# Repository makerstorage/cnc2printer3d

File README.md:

This Project is for the people who have their own desktop CNC machine and wish to use it as a 3D printer. Over the years We have had lots of good feedback about the subject and so decided to develop Hardware and Software solutions for makers. 

For more details, check out the project pages at

https://cnc2printer3d.wordpress.com/

And our store at

http://makerstorage.com/index.php

We enjoy sharing theses ideas with you all and any contributions, comments and or feedback is invited.

Community, Collaboration and Sharing is our most important assets.

This Project is Open Source and is licensed under the Creative Commons 3.0.

https://creativecommons.org/licenses/by-sa/3.0/

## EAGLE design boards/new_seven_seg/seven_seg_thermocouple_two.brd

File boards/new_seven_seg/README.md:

**New Seven Segment Temperature Controller**

For more details, check out the product page at

https://makerstorage.com/index.php?id_product=31&controller=product

MakerStorage invests time and resources providing this open source design, please support MakerStorage and open-source hardware by purchasing products from MakerStorage!

Designed by MakerStorage LLC.

Creative Commons Attribution, Share-Alike license, check https://creativecommons.org/licenses/by-sa/3.0/ for more information All text above must be included in any redistribution

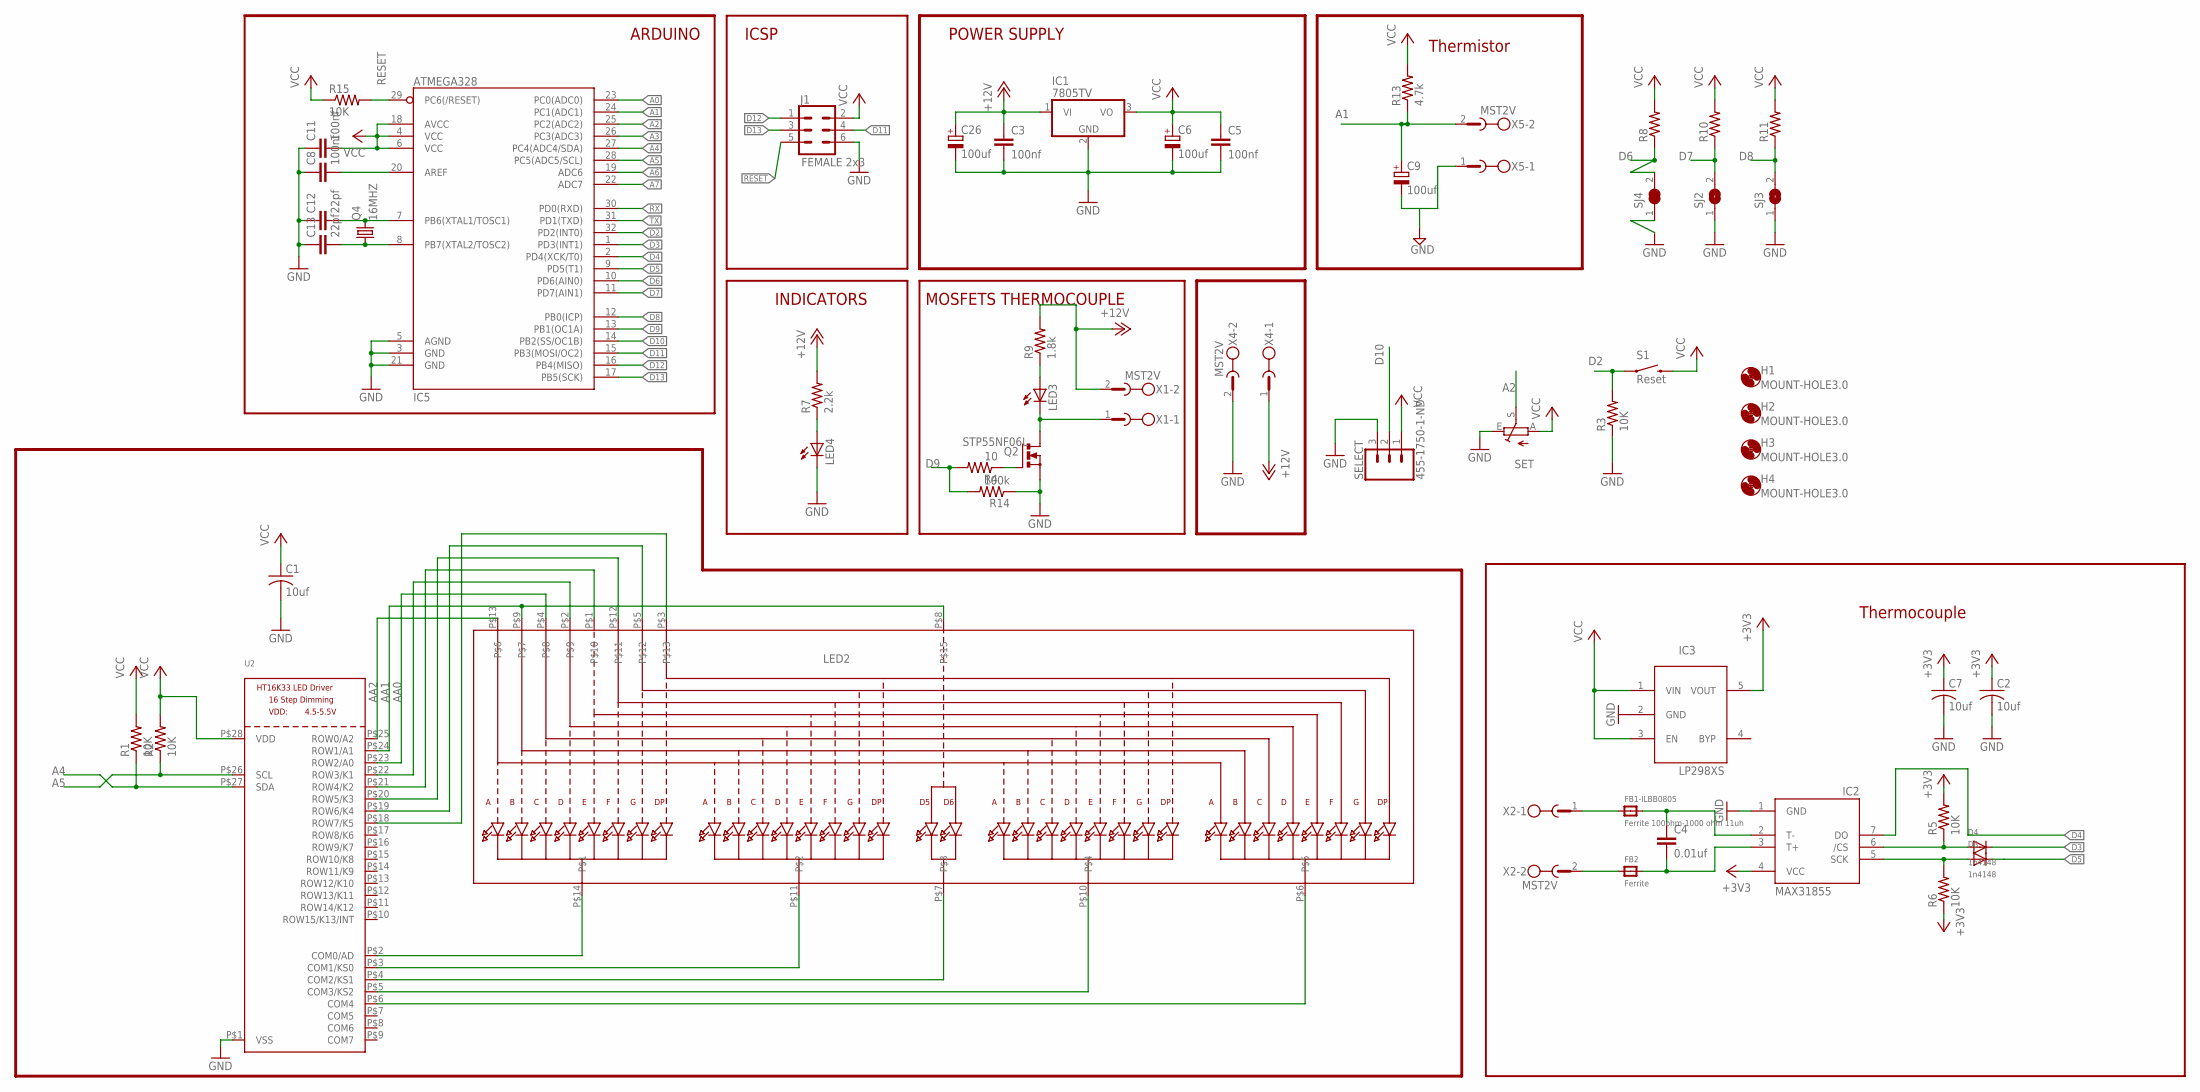
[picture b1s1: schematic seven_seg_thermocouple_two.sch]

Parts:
C1, C2, C7: 10uf; C1206
C3, C5, C8, C11: 100nf; C1206
C4: 0.01uf; C1206
C6, C9, C26: 100uf; PANASONIC_D
C12, C13: 22pf; C1206
D3, D4: 1n4148; SOD-123
FB1-ILBB0805: Ferrite 100ohm-1000 ohm 11uh; _0805
FB2: Ferrite; _0805
H1, H2, H3, H4: MOUNT-HOLE3.0; 3,0
IC1: 7805TV; TO220V
IC2: MAX31855; SO08
IC3: LP298XS; SOT23-5L
IC5: ATMEGA328; TQFP32-08
J1: FEMALE 2x3; 2X3
LED2: DISP_SEGMENT_4DIGIT_BL-Q56C43; SEGMENT-BL-Q56C43
LED3, LED4: LEDCHIPLED_1206; CHIPLED_1206
Q2: STP55NF06L; TO220BV
Q4: 16MHZ; HC49/S
R1, R2, R3, R5, R6, R15: 10K; R1206
R4: 10; R1206
R7: 2.2k; R1206
R8, R10, R11: R-US_R1206; R1206
R9: 1.8k; R1206
R13: 4.7k; R1206
R14: 100k; R1206
S1: Reset; TACTILE-SWITCH-SMD-ALT01
SELECT: 455-1750-1-ND; 1X03
SET: TRIM_EU-B25U; B25U
SJ2, SJ3: SJ
SJ4: SOLDERJUMPER_CLOSED; SOLDERJUMPER_CLOSEDWIRE
U2: HT16K33_SOP28; SOP28_300MIL
X1, X2, X4, X5: MST2V; MSTBV2

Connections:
+3V3: C2.1, C7.1, IC2.4 (VCC), IC3.5 (VOUT), R5.2, R6.1
+12V: C3.1, C26.+, IC1.1 (VI), R7.2, R9.2, X1.2, X4.1
A0: IC5.23 (PC0(ADC0))
A1: C9.+, IC5.24 (PC1(ADC1)), R13.1, X5.2
A2: IC5.25 (PC2(ADC2)), SET.S
A3: IC5.26 (PC3(ADC3))
A4: IC5.27 (PC4(ADC4/SDA)), R1.1, U2.P$27 (SDA)
A5: IC5.28 (PC5(ADC5/SCL)), R2.1, U2.P$26 (SCL)
A6: IC5.19 (ADC6)
A7: IC5.22 (ADC7)
AA0: LED2.P$4, U2.P$23 (ROW2/A0)
AA1: LED2.P$8, LED2.P$9, U2.P$24 (ROW1/A1)
AA2: LED2.P$13, U2.P$25 (ROW0/A2)
CS: D4.A, IC2.6 (/CS), R5.1
D2: IC5.32 (PD2(INT0)), R3.2, S1.1, S1.2 (1)
D3: D4.C, IC5.1 (PD3(INT1))
D4: IC2.7 (DO), IC5.2 (PD4(XCK/T0))
D5: D3.C, IC5.9 (PD5(T1))
D6: IC5.10 (PD6(AIN0)), R8.1, SJ4.2
D7: IC5.11 (PD7(AIN1)), R10.1, SJ2.2
D8: IC5.12 (PB0(ICP)), R11.1, SJ3.2
D9: IC5.13 (PB1(OC1A)), R4.2, R14.2
D10: IC5.14 (PB2(SS/OC1B)), SELECT.2
D11: IC5.15 (PB3(MOSI/OC2)), J1.4
D12: IC5.16 (PB4(MISO)), J1.1
D13: IC5.17 (PB5(SCK)), J1.3
GND: C1.2, C2.2, C3.2, C5.2, C6.-, C7.2, C8.1, C9.-, C11.1, C12.1, C13.1, C26.-, IC1.2 (GND), IC2.1 (GND), IC3.2 (GND), IC5.3 (GND), IC5.5 (AGND), IC5.21 (GND), J1.6, LED4.C, Q2.S, R3.1, R14.1, SELECT.3, SET.E, SJ2.1, SJ3.1, SJ4.1, U2.P$1 (VSS), X4.2, X5.1
unnamed: FB1-ILBB0805.1, X2.1
unnamed: LED2.P$14, U2.P$2 (COM0/AD)
unnamed: LED2.P$11, U2.P$3 (COM1/KS0)
unnamed: LED2.P$7, U2.P$4 (COM2/KS1)
unnamed: LED2.P$10, U2.P$5 (COM3/KS2)
unnamed: LED2.P$6, U2.P$6 (COM4)
unnamed: LED3.C, Q2.D, X1.1
unnamed: C4.1, FB1-ILBB0805.2, IC2.2 (T-)
unnamed: FB2.1, X2.2
unnamed: LED2.P$2, U2.P$22 (ROW3/K1)
unnamed: LED2.P$1, U2.P$21 (ROW4/K2)
unnamed: LED2.P$12, U2.P$20 (ROW5/K3)
unnamed: LED2.P$5, U2.P$19 (ROW6/K4)
unnamed: C4.2, FB2.2, IC2.3 (T+)
unnamed: LED2.P$3, U2.P$18 (ROW7/K5)
unnamed: C8.2, IC5.20 (AREF)
unnamed: LED4.A, R7.1
unnamed: C12.2, IC5.7 (PB6(XTAL1/TOSC1)), Q4.2
unnamed: C13.2, IC5.8 (PB7(XTAL2/TOSC2)), Q4.1
unnamed: LED3.A, R9.1
unnamed: Q2.G, R4.1
RESET: IC5.29 (PC6(/RESET)), J1.5, R15.2
RX: IC5.30 (PD0(RXD))
SCK: D3.A, IC2.5 (SCK), R6.2
TX: IC5.31 (PD1(TXD))
VCC: C1.1, C5.1, C6.+, C11.2, IC1.3 (VO), IC3.1 (VIN), IC3.3 (EN), IC5.4 (VCC), IC5.6 (VCC), IC5.18 (AVCC), J1.2, R1.2, R2.2, R8.2, R10.2, R11.2, R13.2, R15.1, S1.3 (2), S1.4 (2), SELECT.1, SET.A, U2.P$28 (VDD)

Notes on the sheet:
MOSFETS THERMOCOUPLE
ICSP
ARDUINO
INDICATORS
POWER SUPPLY
Thermocouple
Thermistor

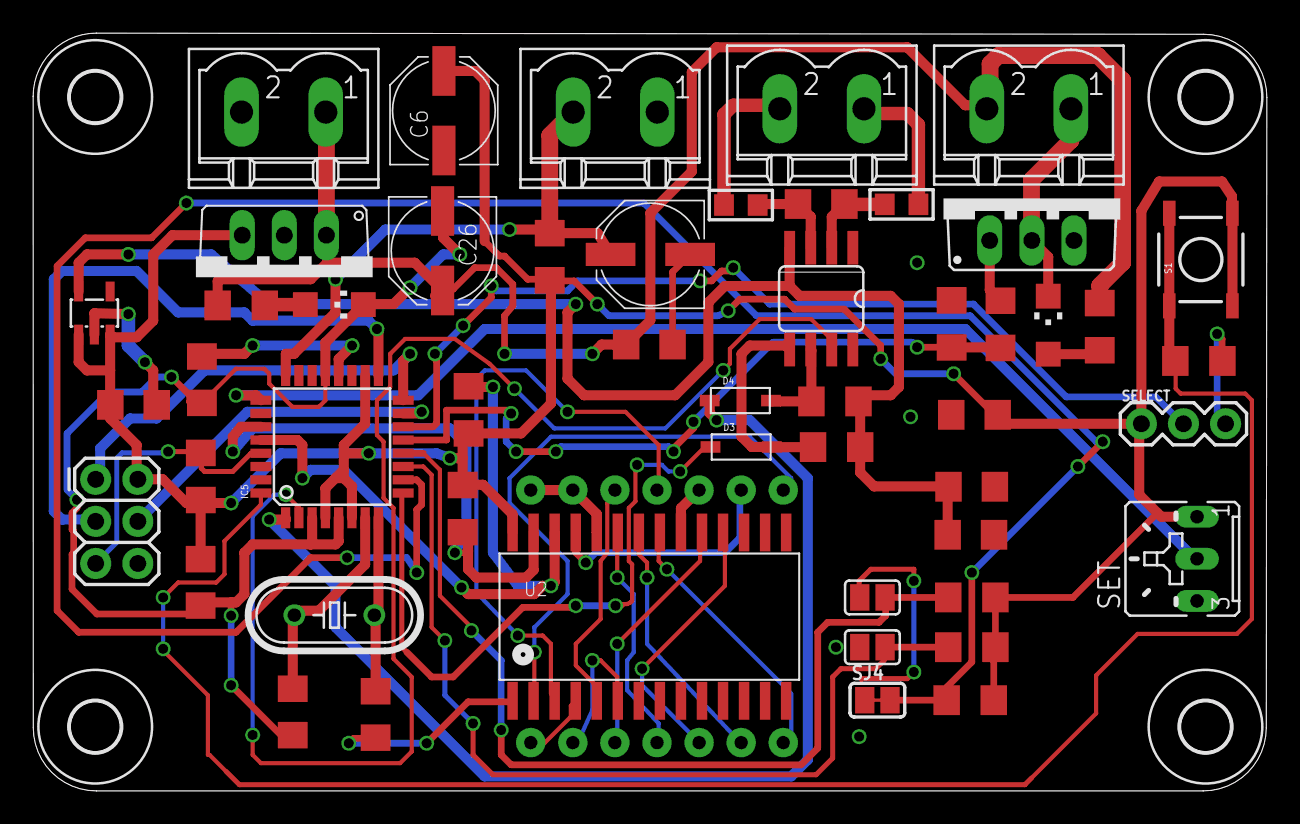
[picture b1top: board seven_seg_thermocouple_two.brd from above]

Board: 2 copper layers, 74.4 x 45.7 mm, 56 parts (1 on the bottom side), 47 nets.

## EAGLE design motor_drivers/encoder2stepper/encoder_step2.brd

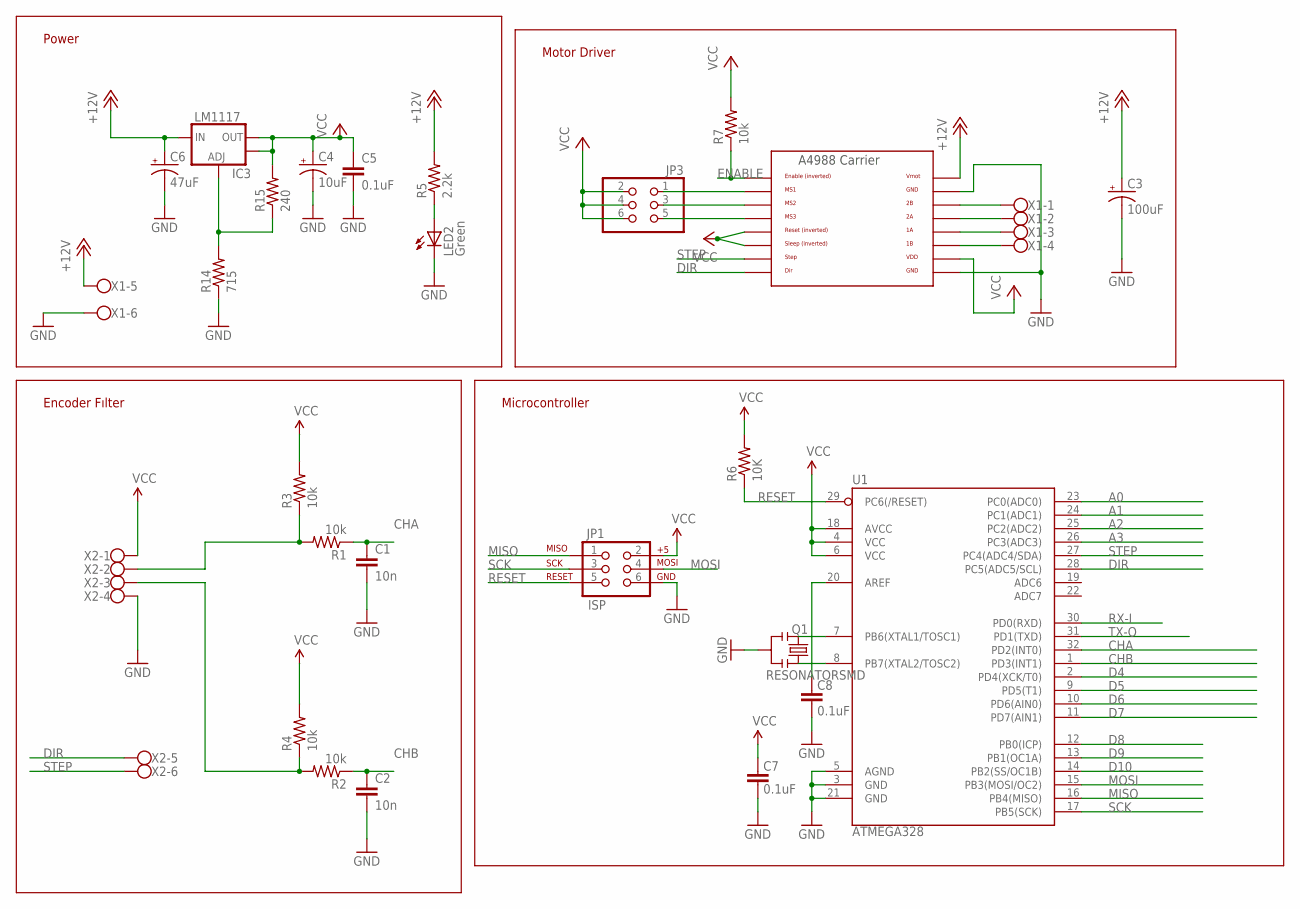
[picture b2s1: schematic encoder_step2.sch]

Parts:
C1, C2: 10n; 0805
C3: 100uF; 153CLV-0605
C4: 10uF; EIA3216
C5, C7, C8: 0.1uF; 0805
C6: 47uF; PANASONIC_D
IC3: LM1117; SOT223-ALT1
JP1: ISP; 2X3
JP3: PINHD-2X3; 2X03
LED2: Green; LED-1206-NO_SILK
Q1: RESONATORSMD; RESONATOR-SMD
R1, R2, R3, R4, R7: 10k; 0805
R5: 2.2k; 0805
R6: 10K; 0805
R14: 715; 0805
R15: 240; 0805
U1: ATMEGA328; TQFP32-08
U$5: A4988BREAKOUT
X1, X2: W237-6

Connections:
+12V: C3.+, C6.+, IC3.3 (IN), R5.2, U$5.VMOT, X1.5
A0: U1.23 (PC0(ADC0))
A1: U1.24 (PC1(ADC1))
A2: U1.25 (PC2(ADC2))
A3: U1.26 (PC3(ADC3))
AREF: C8.2, U1.20 (AREF)
CHA: C1.1, R1.1, U1.32 (PD2(INT0))
CHB: C2.1, R2.1, U1.1 (PD3(INT1))
D4: U1.2 (PD4(XCK/T0))
D5: U1.9 (PD5(T1))
D6: U1.10 (PD6(AIN0))
D7: U1.11 (PD7(AIN1))
D8: U1.12 (PB0(ICP))
D9: U1.13 (PB1(OC1A))
D10: U1.14 (PB2(SS/OC1B))
DIR: U1.28 (PC5(ADC5/SCL)), U$5.DIR, X2.5
ENABLE: R7.1, U$5.EN
GND: C1.2, C2.2, C3.-, C4.C (-), C5.2, C6.-, C7.1, C8.1, JP1.6, LED2.C, Q1.2, R14.1, U1.3 (GND), U1.5 (AGND), U1.21 (GND), U$5.GND, U$5.GND@0 (GND), X1.6, X2.4
MISO: JP1.1, U1.16 (PB4(MISO))
MOSI: JP1.4, U1.15 (PB3(MOSI/OC2))
unnamed: Q1.1, U1.8 (PB7(XTAL2/TOSC2))
unnamed: LED2.A, R5.1
unnamed: R1.2, R3.1, X2.2
unnamed: R2.2, R4.1, X2.3
unnamed: Q1.3, U1.7 (PB6(XTAL1/TOSC1))
unnamed: U$5.2B, X1.1
unnamed: U$5.2A, X1.2
unnamed: IC3.1 (ADJ), R14.2, R15.1
unnamed: U$5.1A, X1.3
unnamed: U$5.1B, X1.4
unnamed: JP3.1, U$5.MS1
unnamed: JP3.5, U$5.MS3
unnamed: JP3.3, U$5.MS2
RESET: JP1.5, R6.1, U1.29 (PC6(/RESET))
RX-I: U1.30 (PD0(RXD))
SCK: JP1.3, U1.17 (PB5(SCK))
STEP: U1.27 (PC4(ADC4/SDA)), U$5.STEP, X2.6
TX-O: U1.31 (PD1(TXD))
VCC: C4.A (+), C5.1, C7.2, IC3.2 (OUT), IC3.4 (OUT), JP1.2, JP3.2, JP3.4, JP3.6, R3.2, R4.2, R6.2, R7.2, R15.2, U1.4 (VCC), U1.6 (VCC), U1.18 (AVCC), U$5.RST, U$5.SLP (SLEEP), U$5.VDD, X2.1

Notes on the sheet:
Power
Encoder Fılter
Motor Driver
Microcontroller

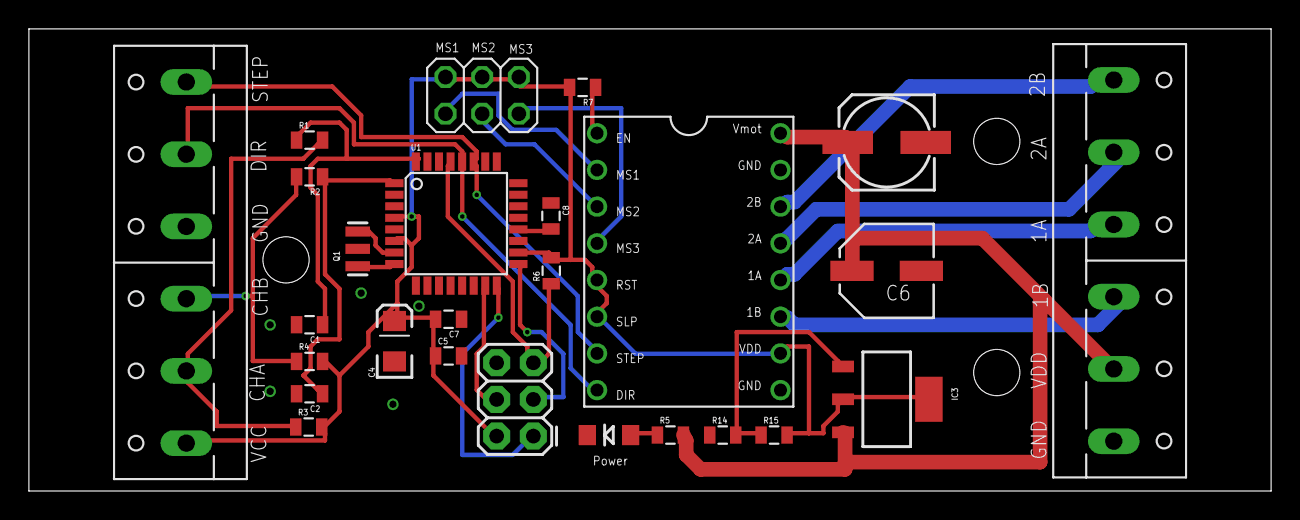
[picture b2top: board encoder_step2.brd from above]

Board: 2 copper layers, 86.0 x 32.0 mm, 26 parts (0 on the bottom side), 26 nets.

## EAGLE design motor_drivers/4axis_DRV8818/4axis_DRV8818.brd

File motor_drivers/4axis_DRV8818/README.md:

DRV8818 4 Axis Stepper Motor Driver Board

For more details, check out the product pages at

http://makerstorage.com/index.php?id_product=21&controller=product

MakerStorage invests time and resources providing this open source design, please support MakerStorage and open-source hardware by purchasing products from MakerStorage!

Designed by MakerStorage LLC.

Creative Commons Attribution, Share-Alike license, check https://creativecommons.org/licenses/by-sa/3.0/ for more information All text above must be included in any redistribution

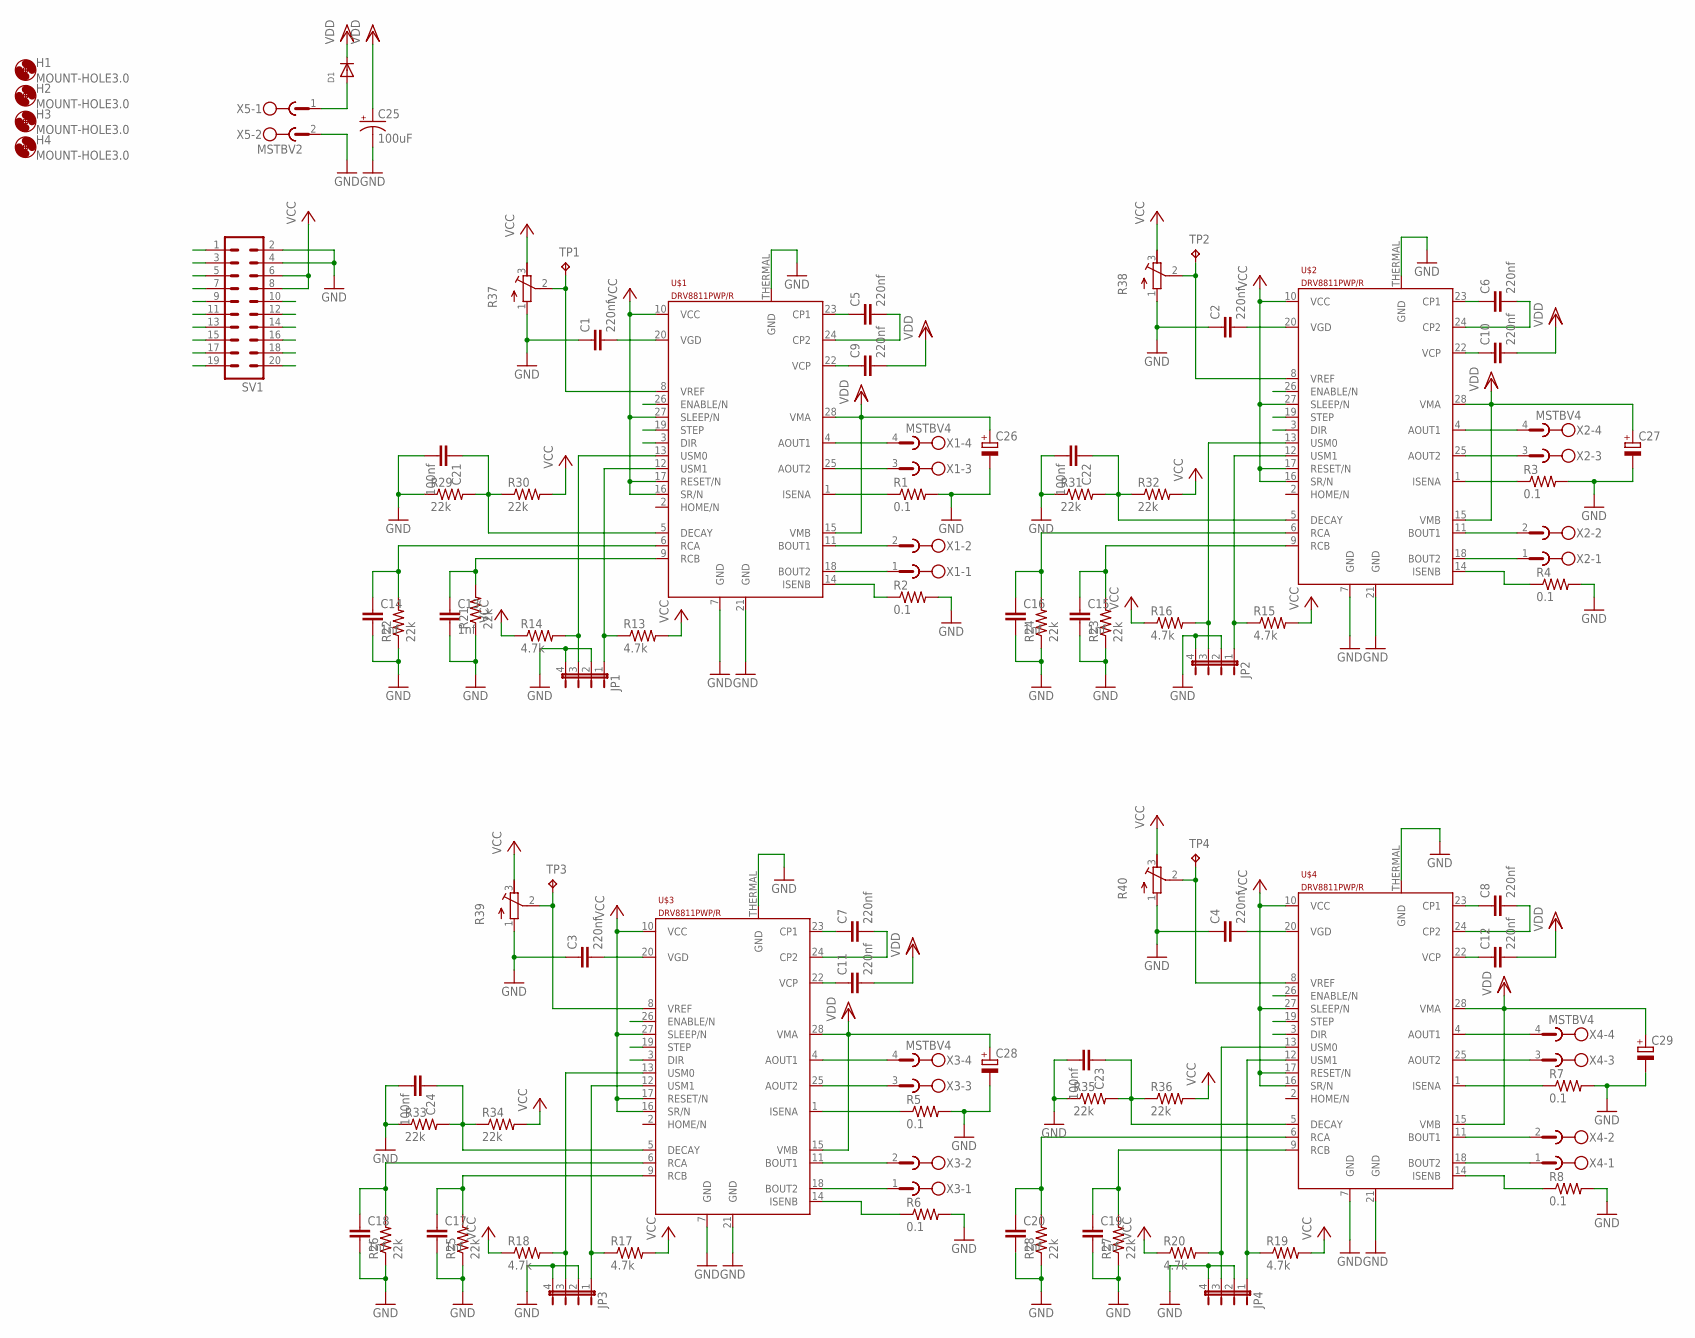
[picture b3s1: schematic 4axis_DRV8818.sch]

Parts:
C1, C2, C3, C4, C5, C6, C7, C8, C9, C10, C11, C12: 220nf; C1206
C13, C14, C15, C16, C17, C18, C19, C20: 1nf; C1206
C21, C22, C23, C24: 100nf; C1206
C25: 100uF; NIC_10X10.5_CAP
C26, C27, C28, C29: CPOL-EUD; PANASONIC_D
D1: DIODESMA; SMADIODE
H1, H2, H3, H4: MOUNT-HOLE3.0; 3,0
JP1, JP2, JP3, JP4: JP4E; JP4
R1, R2, R3, R4, R5, R6, R7, R8: 0.1; R2512
R13, R14, R15, R16, R17, R18, R19, R20: 4.7k; R1206
R21, R22, R23, R24, R25, R26, R27, R28, R29, R30, R31, R32, R33, R34, R35, R36: 22k; R1206
R37, R38, R39, R40: R-TRIMM3103; RTRIM3103
SV1: ML20
TP1, TP2, TP3, TP4: TPTP20R; TP20R
U$1, U$2, U$3, U$4: DRV8811PWP/R; HTSSOP28
X1, X2, X3, X4: MSTBV4
X5: MSTBV2

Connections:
E-DıR: SV1.14, U$4.3 (DIR)
E-EN: SV1.16, U$4.26 (ENABLE/N)
E-ERR: SV1.10
E-ISENA: R7.1, U$4.1 (ISENA)
E-ISENB: R8.1, U$4.14 (ISENB)
E-STEP: SV1.12, U$4.19 (STEP)
GND: C1.1, C2.1, C3.1, C4.1, C13.2, C14.2, C15.2, C16.2, C17.2, C18.2, C19.2, C20.2, C21.2, C22.2, C23.2, C24.2, C25.-, C26.-, C27.-, C28.-, C29.-, JP1.2, JP1.4, JP2.2, JP2.4, JP3.2, JP3.4, JP4.2, JP4.4, R1.2, R2.2, R3.2, R4.2, R5.2, R6.2, R7.2, R8.2, R21.1, R22.1, R23.1, R24.1, R25.1, R26.1, R27.1, R28.1, R29.1, R31.1, R33.1, R35.1, R37.1 (A), R38.1 (A), R39.1 (A), R40.1 (A), SV1.2, SV1.4, U$1.7 (GND), U$1.21 (GND), U$1.THERMAL (GND), U$2.7 (GND), U$2.21 (GND), U$2.THERMAL (GND), U$3.7 (GND), U$3.21 (GND), U$3.THERMAL (GND), U$4.7 (GND), U$4.21 (GND), U$4.THERMAL (GND), X5.2
unnamed: C4.2, U$4.20 (VGD)
unnamed: C2.2, U$2.20 (VGD)
unnamed: C1.2, U$1.20 (VGD)
unnamed: U$1.4 (AOUT1), X1.4
unnamed: U$1.25 (AOUT2), X1.3
unnamed: U$1.11 (BOUT1), X1.2
unnamed: U$1.18 (BOUT2), X1.1
unnamed: U$2.4 (AOUT1), X2.4
unnamed: U$2.25 (AOUT2), X2.3
unnamed: U$2.11 (BOUT1), X2.2
unnamed: U$2.18 (BOUT2), X2.1
unnamed: U$4.4 (AOUT1), X4.4
unnamed: U$4.25 (AOUT2), X4.3
unnamed: U$4.11 (BOUT1), X4.2
unnamed: U$4.18 (BOUT2), X4.1
unnamed: U$3.4 (AOUT1), X3.4
unnamed: U$3.25 (AOUT2), X3.3
unnamed: U$3.11 (BOUT1), X3.2
unnamed: U$3.18 (BOUT2), X3.1
unnamed: C3.2, U$3.20 (VGD)
unnamed: C5.1, U$1.23 (CP1)
unnamed: C5.2, U$1.24 (CP2)
unnamed: C6.1, U$2.23 (CP1)
unnamed: C6.2, U$2.24 (CP2)
unnamed: C8.1, U$4.23 (CP1)
unnamed: C8.2, U$4.24 (CP2)
unnamed: C7.1, U$3.23 (CP1)
unnamed: C7.2, U$3.24 (CP2)
unnamed: C9.1, U$1.22 (VCP)
unnamed: C10.1, U$2.22 (VCP)
unnamed: C12.1, U$4.22 (VCP)
unnamed: C11.1, U$3.22 (VCP)
unnamed: R38.2 (S), TP2.TP, U$2.8 (VREF)
unnamed: R37.2 (S), TP1.TP, U$1.8 (VREF)
unnamed: R39.2 (S), TP3.TP, U$3.8 (VREF)
unnamed: JP1.3, R14.2, U$1.13 (USM0)
unnamed: R40.2 (S), TP4.TP, U$4.8 (VREF)
unnamed: JP1.1, R13.1, U$1.12 (USM1)
unnamed: JP2.1, R15.1, U$2.12 (USM1)
unnamed: JP2.3, R16.2, U$2.13 (USM0)
unnamed: JP3.1, R17.1, U$3.12 (USM1)
unnamed: JP3.3, R18.2, U$3.13 (USM0)
unnamed: JP4.1, R19.1, U$4.12 (USM1)
unnamed: JP4.3, R20.2, U$4.13 (USM0)
unnamed: C15.1, R23.2, U$2.9 (RCB)
unnamed: C16.1, R24.2, U$2.6 (RCA)
unnamed: C13.1, R21.2, U$1.9 (RCB)
unnamed: C14.1, R22.2, U$1.6 (RCA)
unnamed: C17.1, R25.2, U$3.9 (RCB)
unnamed: C18.1, R26.2, U$3.6 (RCA)
unnamed: C19.1, R27.2, U$4.9 (RCB)
unnamed: C20.1, R28.2, U$4.6 (RCA)
unnamed: C21.1, R29.2, R30.1, U$1.5 (DECAY)
unnamed: C22.1, R31.2, R32.1, U$2.5 (DECAY)
unnamed: C24.1, R33.2, R34.1, U$3.5 (DECAY)
unnamed: C23.1, R35.2, R36.1, U$4.5 (DECAY)
unnamed: D1.A, X5.1
VCC: R13.2, R14.1, R15.2, R16.1, R17.2, R18.1, R19.2, R20.1, R30.2, R32.2, R34.2, R36.2, R37.3 (E), R38.3 (E), R39.3 (E), R40.3 (E), SV1.6, SV1.8, U$1.10 (VCC), U$1.16 (SR/N), U$1.17 (RESET/N), U$1.27 (SLEEP/N), U$2.10 (VCC), U$2.16 (SR/N), U$2.17 (RESET/N), U$2.27 (SLEEP/N), U$3.10 (VCC), U$3.16 (SR/N), U$3.17 (RESET/N), U$3.27 (SLEEP/N), U$4.10 (VCC), U$4.16 (SR/N), U$4.17 (RESET/N), U$4.27 (SLEEP/N)
VDD: C9.2, C10.2, C11.2, C12.2, C25.+, C26.+, C27.+, C28.+, C29.+, D1.C, U$1.15 (VMB), U$1.28 (VMA), U$2.15 (VMB), U$2.28 (VMA), U$3.15 (VMB), U$3.28 (VMA), U$4.15 (VMB), U$4.28 (VMA)
X-DıR: SV1.3, U$1.3 (DIR)
X-EN: SV1.1, U$1.26 (ENABLE/N)
X-ERR: SV1.7
X-ISENA: R1.1, U$1.1 (ISENA)
X-STEP: SV1.5, U$1.19 (STEP)
XISENB: R2.1, U$1.14 (ISENB)
Y-DıR: SV1.11, U$2.3 (DIR)
Y-EN: SV1.9, U$2.26 (ENABLE/N)
Y-ERR: SV1.15
Y-ISENA: R3.1, U$2.1 (ISENA)
Y-ISENB: R4.1, U$2.14 (ISENB)
Y-STEP: SV1.13, U$2.19 (STEP)
Z-DıR: SV1.19, U$3.3 (DIR)
Z-EN: SV1.17, U$3.26 (ENABLE/N)
Z-ERR: SV1.18
Z-ISENA: R5.1, U$3.1 (ISENA)
Z-ISENB: R6.1, U$3.14 (ISENB)
Z-STEP: SV1.20, U$3.19 (STEP)

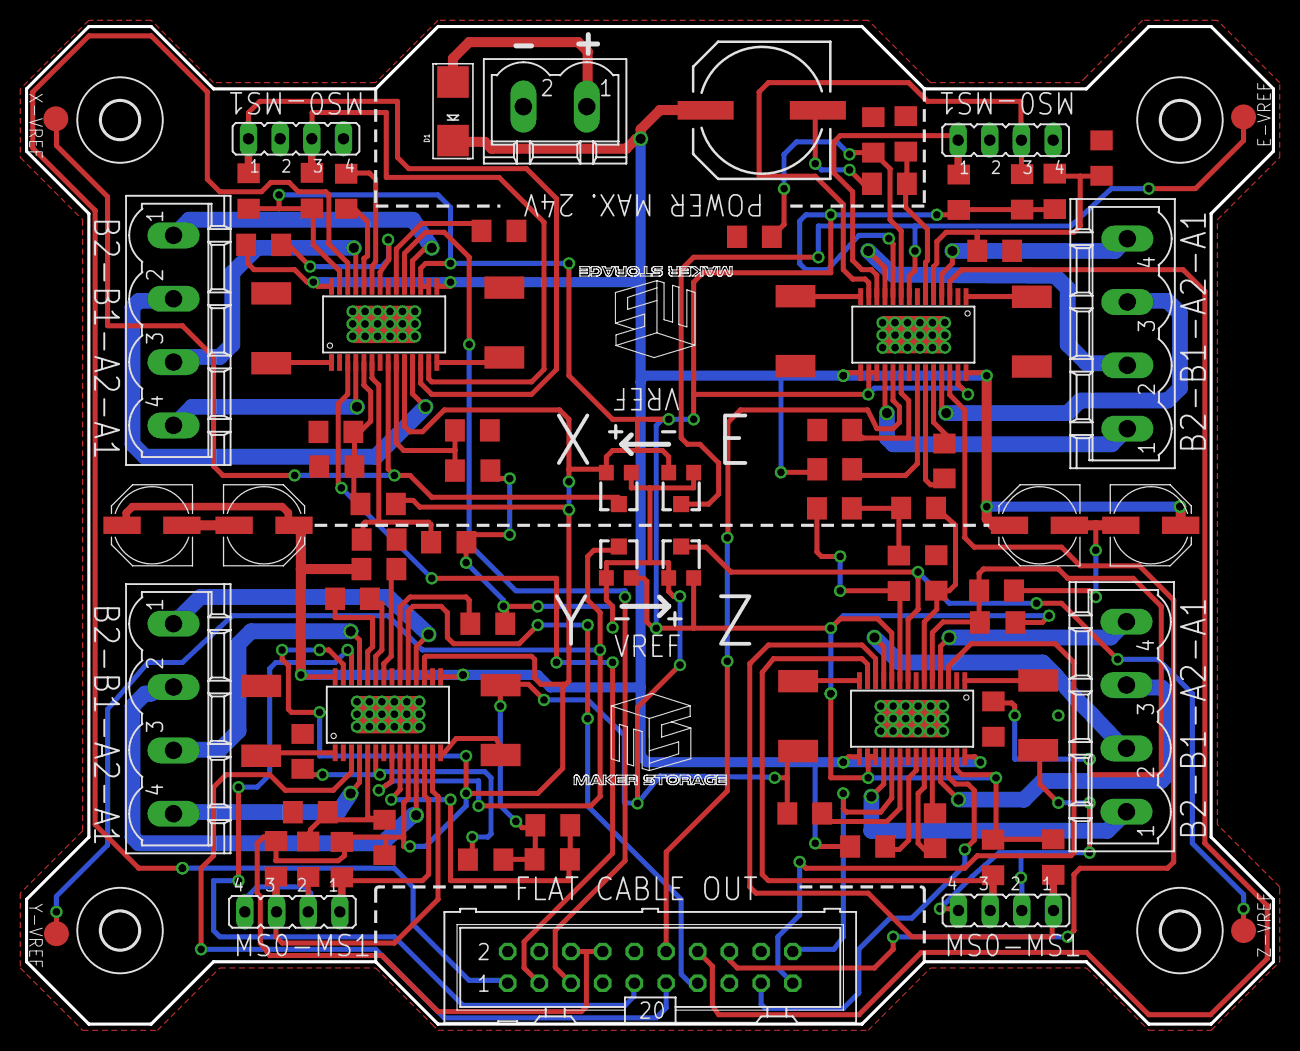
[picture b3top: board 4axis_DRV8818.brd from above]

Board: 2 copper layers, 100.0 x 80.0 mm, 88 parts (0 on the bottom side), 80 nets.

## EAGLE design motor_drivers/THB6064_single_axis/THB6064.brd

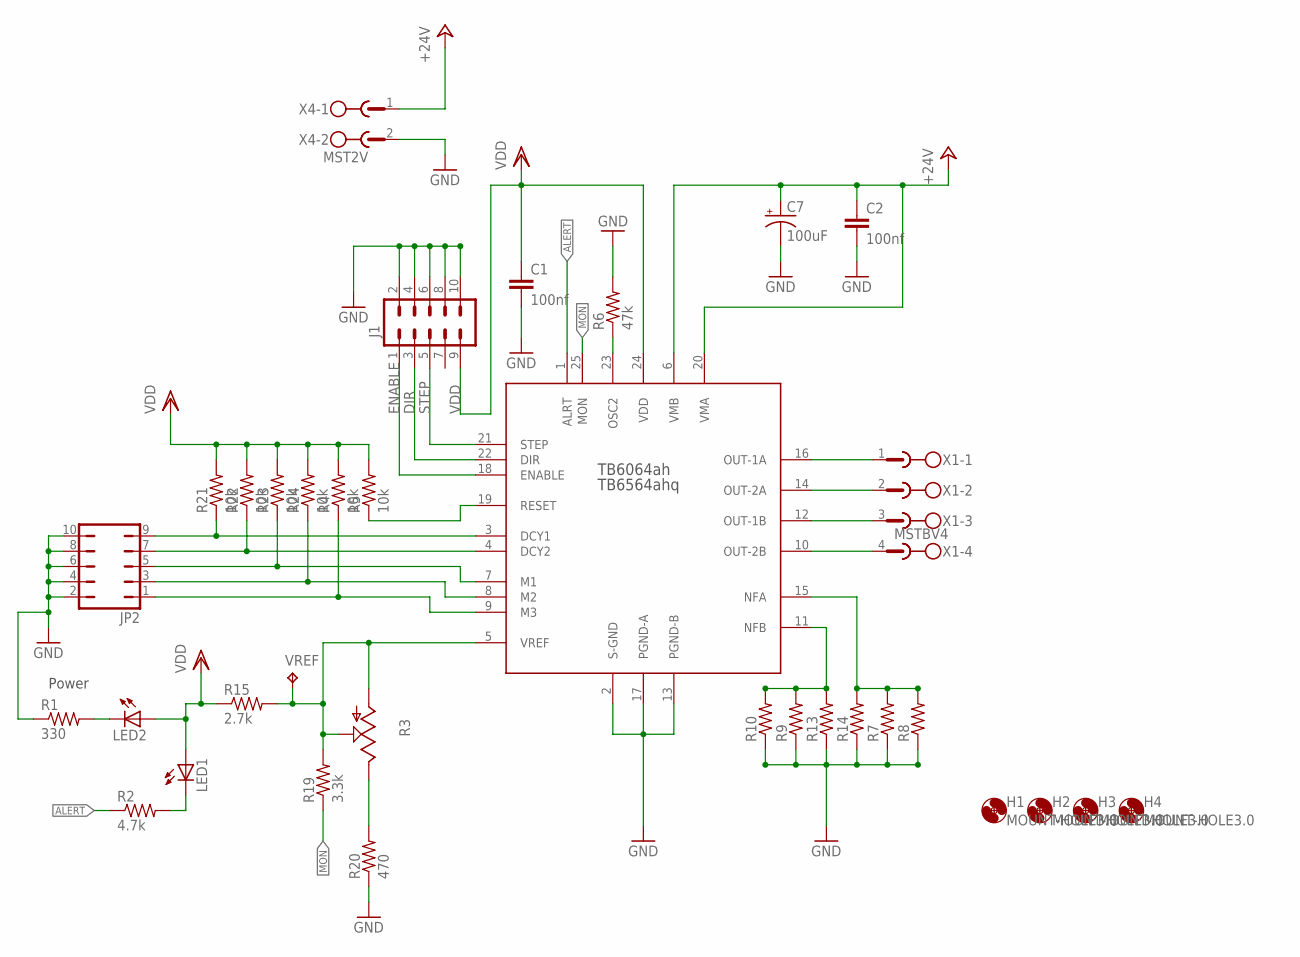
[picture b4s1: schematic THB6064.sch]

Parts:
C1, C2: 100nf; C1206
C7: 100uF; NIC_10X10.5_CAP
H1, H2, H3, H4: MOUNT-HOLE3.0; 3,0
J1: M05X2SHD; 2X5-SHROUDED
JP2: JP5Q
LED1, LED2: LED_E; LED_1206
R1: 330; R1206
R2: 4.7k; R1206
R3: TRIM_US-CA6V; CA6V
R4, R5, R21, R22, R23, R24: 10k; R1206
R6: 47k; R1206
R7, R8, R9, R10, R13, R14: R-US_R2512; R2512
R15: 2.7k; R1206
R19: 3.3k; R1206
R20: 470; R1206
U$1: THB6064; ZIP25
VREF: TPPAD1-17; P1-17
X1: MSTBV4
X4: MST2V; MSTBV2

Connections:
+24V: C2.1, C7.+, U$1.6 (VMB), U$1.20 (VMA), X4.1
ALERT: R2.1, U$1.1 (ALRT)
DIR: J1.3, U$1.22 (DIR)
ENABLE: J1.1, U$1.18 (ENABLE)
GND: C1.2, C2.2, C7.-, J1.2, J1.4, J1.6, J1.8, J1.10, JP2.2, JP2.4, JP2.6, JP2.8, JP2.10, R1.1, R6.2, R7.1, R8.1, R9.1, R10.1, R13.1, R14.1, R20.1, U$1.2 (S-GND), U$1.13 (PGND-B), U$1.17 (PGND-A), X4.2
MON: R19.1, U$1.25 (MON)
unnamed: R9.2, R10.2, R13.2, U$1.11 (NFB)
unnamed: R7.2, R8.2, R14.2, U$1.15 (NFA)
unnamed: R3.E, R20.2
unnamed: R5.1, U$1.19 (RESET)
unnamed: U$1.16 (OUT-1A), X1.1
unnamed: JP2.9, R21.1, U$1.3 (DCY1)
unnamed: R6.1, U$1.23 (OSC2)
unnamed: JP2.7, R22.1, U$1.4 (DCY2)
unnamed: JP2.5, R23.1, U$1.7 (M1)
unnamed: JP2.3, R24.1, U$1.8 (M2)
unnamed: JP2.1, R4.1, U$1.9 (M3)
unnamed: U$1.14 (OUT-2A), X1.2
unnamed: U$1.12 (OUT-1B), X1.3
unnamed: U$1.10 (OUT-2B), X1.4
unnamed: LED2.C, R1.2
unnamed: LED1.C, R2.2
unnamed: R3.A, R3.S, R15.2, R19.2, U$1.5 (VREF), VREF.TP
STEP: J1.5, U$1.21 (STEP)
VDD: C1.1, J1.9, LED1.A, LED2.A, R4.2, R5.2, R15.1, R21.2, R22.2, R23.2, R24.2, U$1.24 (VDD)

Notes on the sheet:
Power

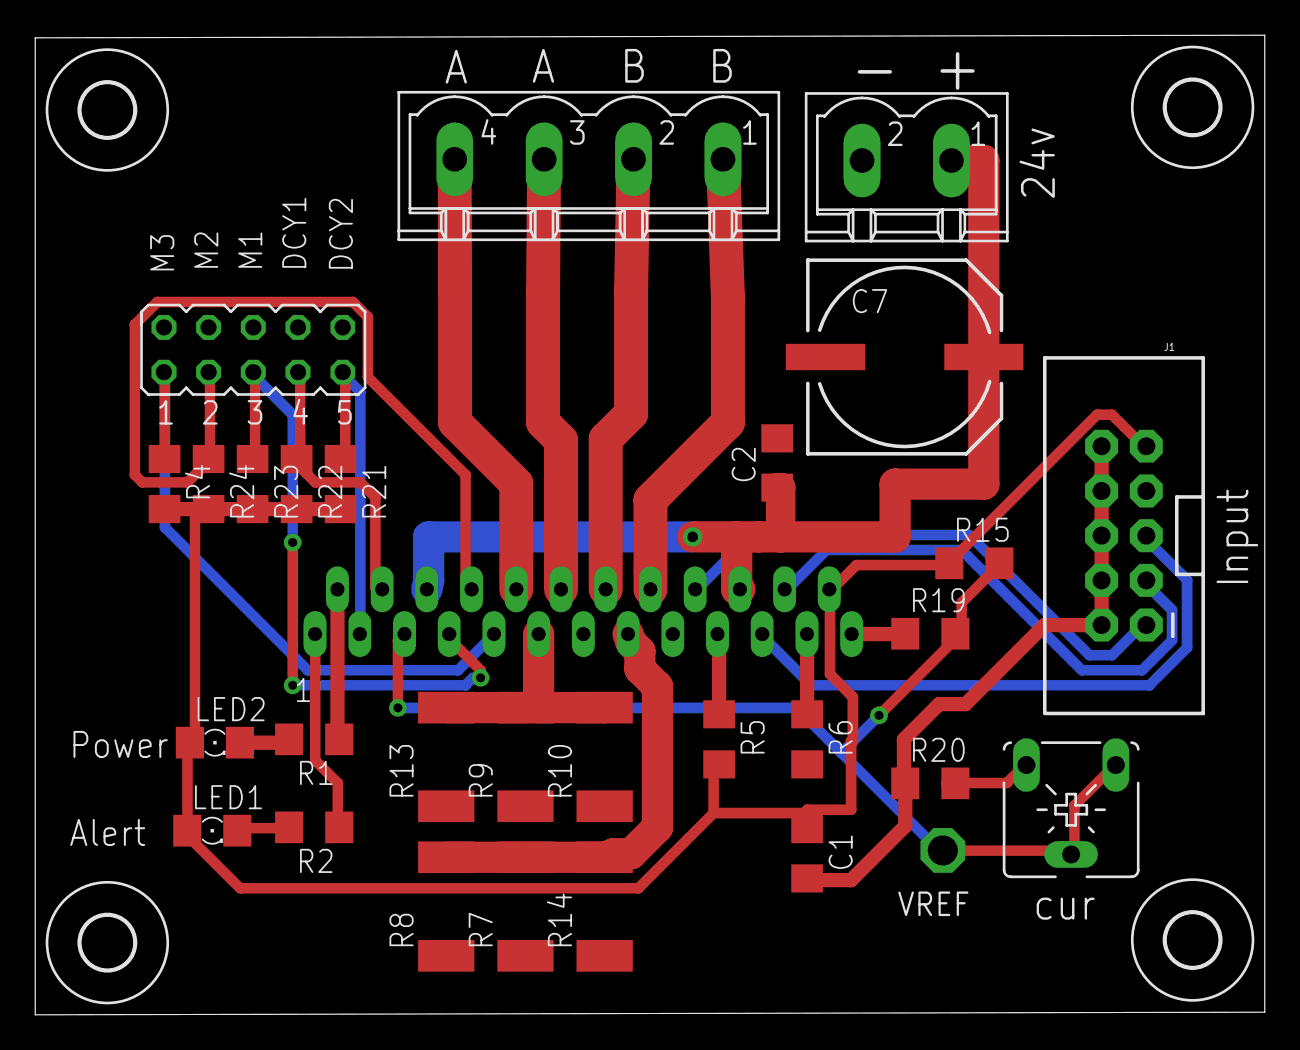
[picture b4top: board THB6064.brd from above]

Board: 2 copper layers, 69.8 x 55.6 mm, 34 parts (0 on the bottom side), 25 nets.

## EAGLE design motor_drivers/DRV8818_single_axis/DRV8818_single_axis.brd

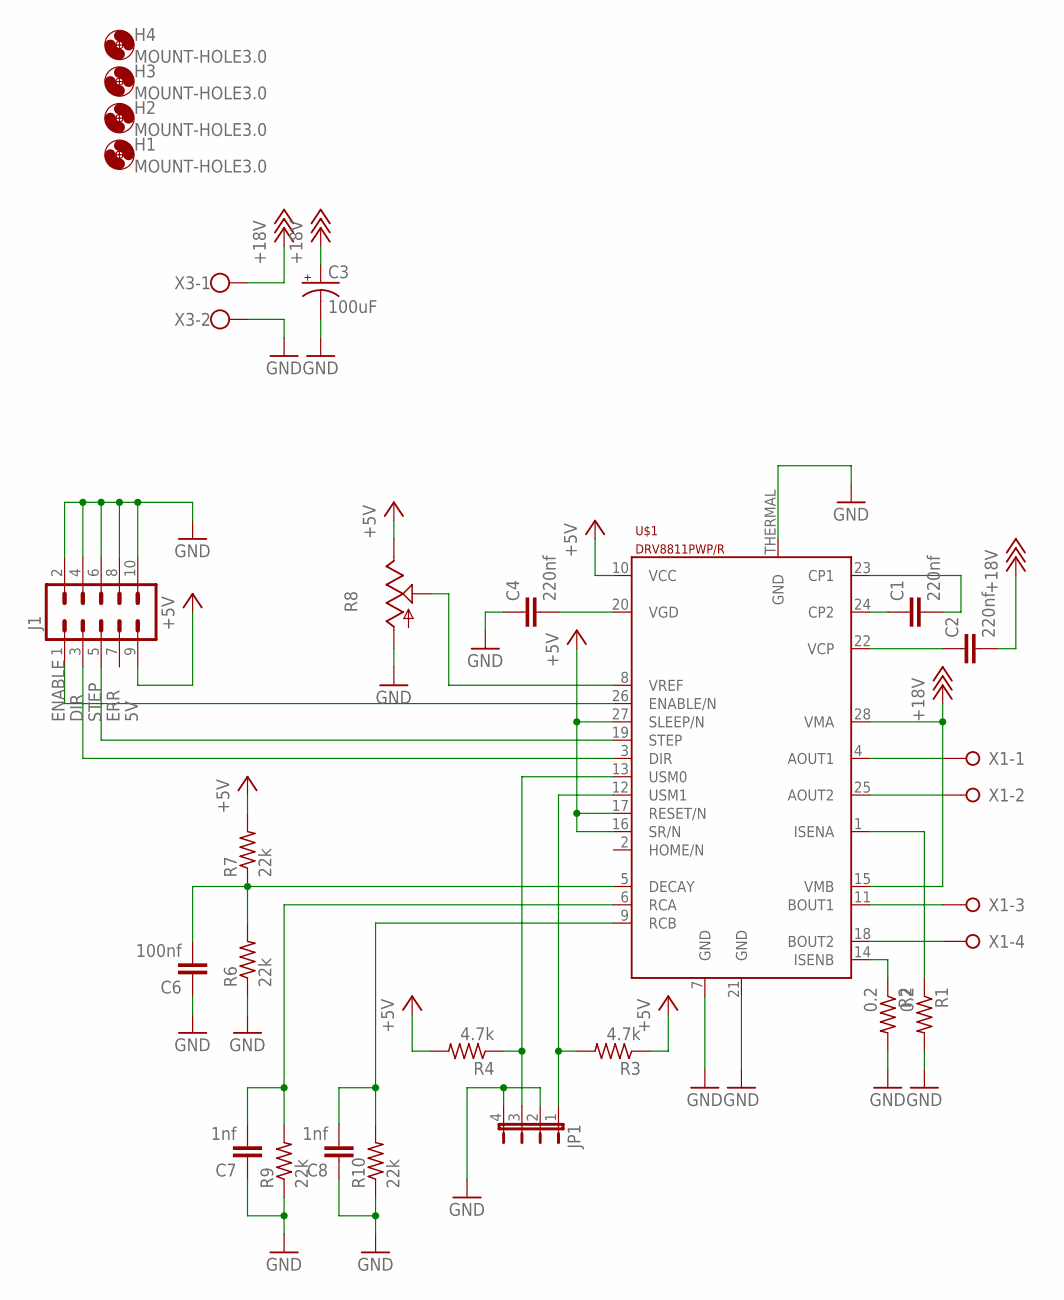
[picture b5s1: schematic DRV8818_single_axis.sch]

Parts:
C1, C2, C4: 220nf; C1206
C3: 100uF; NIC_10X10.5_CAP
C6: 100nf; C1206
C7, C8: 1nf; C1206
H1, H2, H3, H4: MOUNT-HOLE3.0; 3,0
J1: M05X2SHD_LOCK; 2X5-SHROUDED_LOCK
JP1: JP4E; JP4
R1, R2: 0.2; R2512
R3, R4: 4.7k; R1206
R6, R7, R9, R10: 22k; R1206
R8: TRIM_US-CA6V; CA6V
U$1: DRV8811PWP/R; HTSSOP28
X1: W237-04P; W237-4P
X3: W237-102

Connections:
+5V: J1.9, R3.1, R4.2, R7.2, R8.E, U$1.10 (VCC), U$1.16 (SR/N), U$1.17 (RESET/N), U$1.27 (SLEEP/N)
+18V: C2.2, C3.+, U$1.15 (VMB), U$1.28 (VMA), X3.1
DIR: J1.3, U$1.3 (DIR)
ENABLE: J1.1, U$1.26 (ENABLE/N)
GND: C3.-, C4.1, C6.1, C7.1, C8.1, J1.2, J1.4, J1.6, J1.8, J1.10, JP1.2, JP1.4, R1.2, R2.2, R6.1, R8.A, R9.1, R10.1, U$1.7 (GND), U$1.21 (GND), U$1.THERMAL (GND), X3.2
ISENA: R1.1, U$1.1 (ISENA)
ISENB: R2.1, U$1.14 (ISENB)
unnamed: U$1.11 (BOUT1), X1.3
unnamed: U$1.18 (BOUT2), X1.4
unnamed: U$1.4 (AOUT1), X1.1
unnamed: U$1.25 (AOUT2), X1.2
unnamed: C1.1, U$1.24 (CP2)
unnamed: C1.2, U$1.23 (CP1)
unnamed: C4.2, U$1.20 (VGD)
unnamed: JP1.1, R3.2, U$1.12 (USM1)
unnamed: C2.1, U$1.22 (VCP)
unnamed: JP1.3, R4.1, U$1.13 (USM0)
unnamed: C6.2, R6.2, R7.1, U$1.5 (DECAY)
unnamed: C8.2, R10.2, U$1.9 (RCB)
unnamed: C7.2, R9.2, U$1.6 (RCA)
STEP: J1.5, U$1.19 (STEP)
VREF: R8.S, U$1.8 (VREF)

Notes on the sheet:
ENABLE
DIR
STEP
ERR

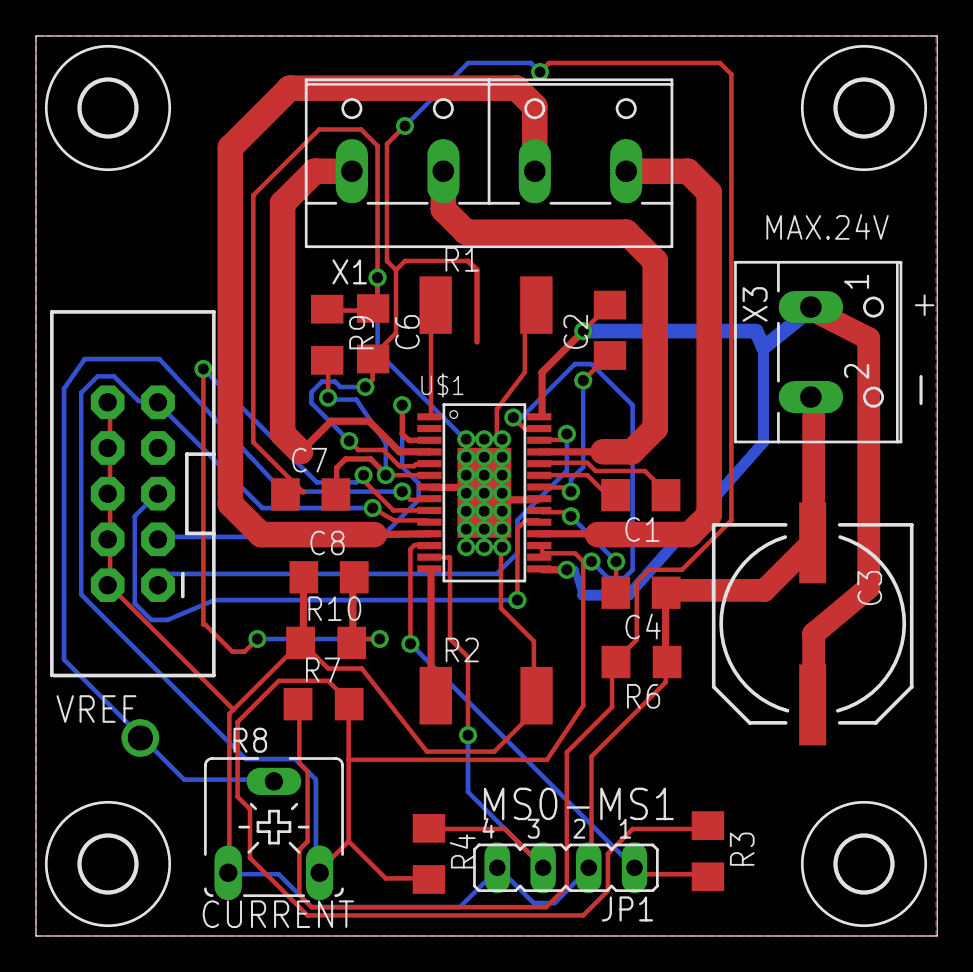
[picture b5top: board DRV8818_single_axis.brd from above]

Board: 2 copper layers, 50.1 x 50.0 mm, 25 parts (0 on the bottom side), 22 nets.

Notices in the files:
parts and their libraries:
SparkFun-Connectors: Licensing: Creative Commons ShareAlike 4.0 International - https://creativecommons.org/licenses/by-sa/4.0
SparkFun-LED: Licensing: CC v3.0 Share-Alike You are welcome to use this library for commercial purposes.
